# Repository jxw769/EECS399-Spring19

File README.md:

# EECS399_Spring19
Senior Project II for EECS399 in Spring 2019.

## Updated DDS Project 
In folder `DE10_Standard_AD9913`. Changed board to DE10 Standard from DE1. <br/>**See [DE10 setup](/DE10_Standard_AD9913/documentation/de10_setup.md) for the setup tutorial.**

EAGLE PCB Files and component datasheets are in `AD9913_PCB`.

## Bluetooth SPP Android App
`btspp.aia` is the Thunkable based Android app that can display scanning images via Bluetooth. Image data via Bluetooth is parsed to JSON from text format and converted to orignal PNG type from base64 JSON string. The app supports continous transmission and display of the scanning images, with a FPS around 0.5~1 due to Bluetooth transmission rate limit. *Can only be imported to [Thunkable Classic Platform](http://app.thunkable.com/?locale=en) (Not Cross Platform ver.).*

### How to use it
#### DE10 SoC Setup
* **Make sure DE10 switch setup is the same as below**
    </br>
* Boot up the Linux system.
* Configure Linux such that the device is paired and bluetooth SPP port is enabled. (See below and Ref)
* Execute
```cd ~/eecs399/bluetooth_send/ ```</br>
```./service.py```
  
#### Configuring Bluetooth on Linux
* Management of paired devices is done by bluetoothctl. (Configure etc/bluetooth/main.conf first)
* Once device is paired, we need to open up SPP upon reboot. A sample supervisor file can be found under `supervisor_conf`. If SPP port is not added, bluetooth transmission will not initiate. 
* Dependencies of service.py include PyBluez (for Python3).

#### Service.py
This file is written in mind that in the future, auto-detection of carotid function will be added to the service. The directory in which scanned image file is read and transmitted can be changed. 
One problem with this service file is that no time-out function is added. Therefore if a device is connected and not used (or, more likely, the app suddenly crashed without disconnecting the service), the service file will sit there forever, and must be restarted on Linux. This is not ideal for a product, and the best way is to add a time-out function, i.e. to have De10 automatically disconnect with the Android device if it doesn't receive any command from Android for a certain period of time. 

### Android App
* Press **Connect** to connect with a paired device (DE10 for current use).
* **Scan** to accept image data transmission via Bluetooth. Image are displayed in the (currently disabled) *Log* section. 
    * Scroll down *Log* to see activity history.
* **Stop** to stop accepting images. 
* **Proceed** to stop accepting images and proceed to the next task. 
* **Clear** to clear *Log* section and delete stored image data.
* **Disconnect** to disconnect from current connected device.

### Screenshots

### References
1. Thunkable Sample Bluetooth Chat App
`btchat.aia` is a sample Android app for Bluetooth SPP communication. It supports tranferring and receiving text data from connected devices. 
2. Used extensions: 
    * JSONTools: https://community.thunkable.com/t/free-jsontools-extension-version-4-released/5447
    * SimpleBase64: https://groups.google.com/d/msg/mitappinventortest/TAkRiwgY1yI/wQBnn6E0CwAJ
    * PyBluez
3. Configure Bluetooth on Linux
Here are some links that we found useful in setting up bluetooth:
    * Linux Bluetoothctl https://www.intel.com/content/dam/support/us/en/documents/edison/sb/edisonbluetooth_331704007.pdf
    * Setup SPP port (and use RFCOMM) https://unix.stackexchange.com/questions/92255/how-do-i-connect-and-send-data-to-a-bluetooth-serial-port-on-linux
    * Using PyBluez https://people.csail.mit.edu/albert/bluez-intro/x232.html

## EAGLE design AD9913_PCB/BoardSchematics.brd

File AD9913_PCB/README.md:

These are the most up-to-date EAGLE PCB files. 
One Problem with our design is that the comparator outputs needs to be pulled down to Vdd-2V, and we tried to use a linear regulator for this purpose. The problem is, however, that linear regulators cannot sink current, and therefore our comparator output would drag the 1.2 V linear regulator output to 3.3 V on which the comparator is run. One workaround is to add a small resistor from the linear regulator's output to ground, and therefore making the linear regulator always source current. This is not a good idea and is only a temporary workaround. Please redesign this part of the circuit.

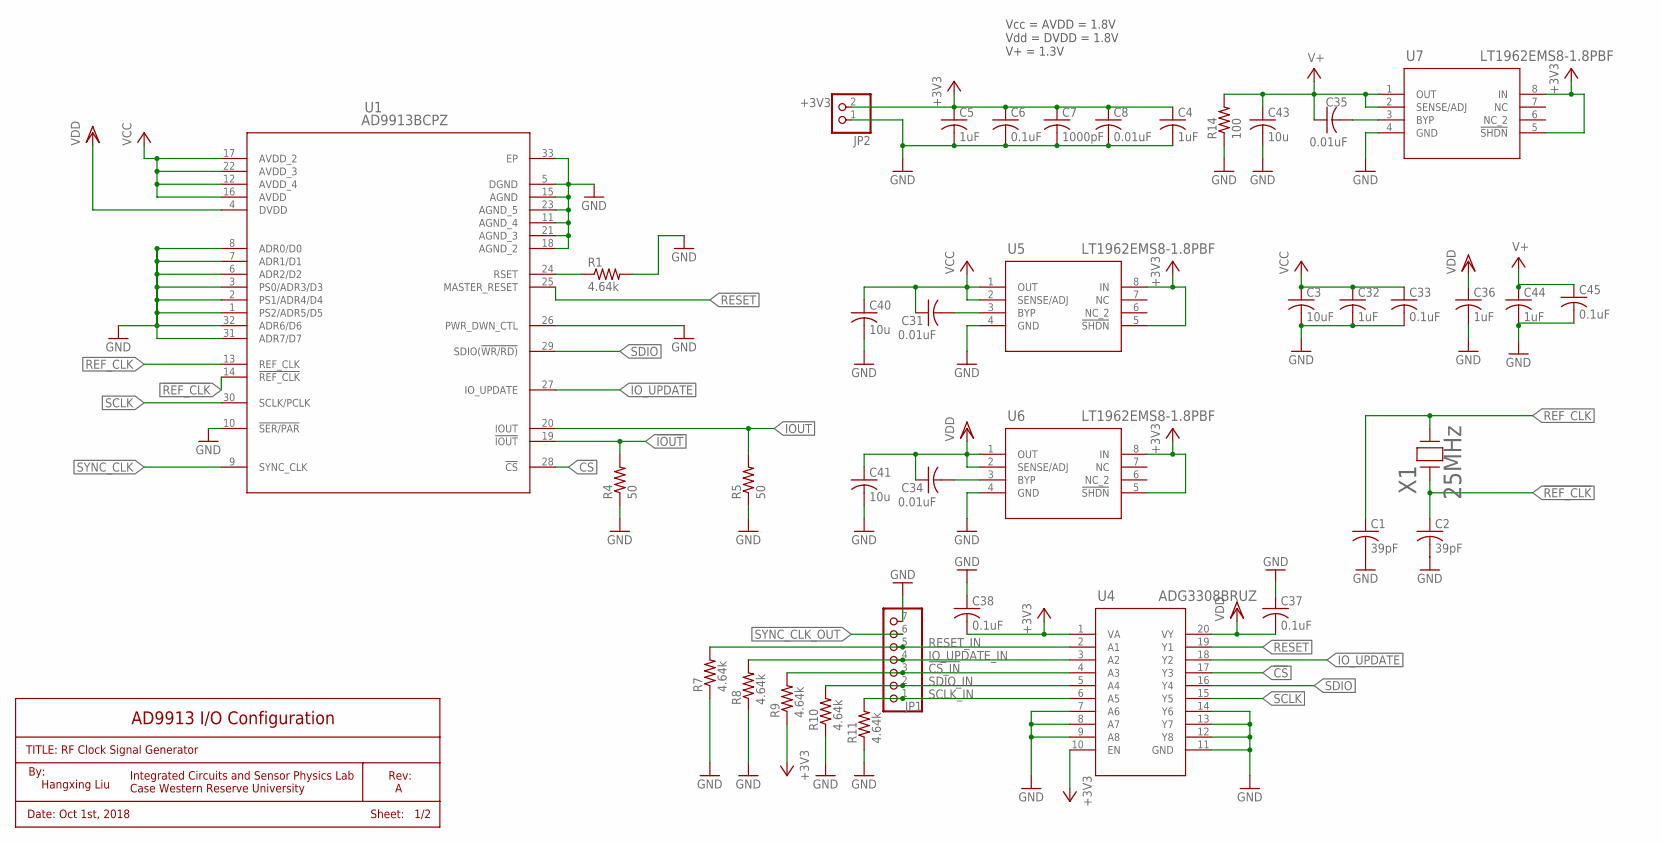
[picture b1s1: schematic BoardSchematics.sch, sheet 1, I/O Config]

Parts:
C1, C2: 39pF; C1608
C3: 10uF; C0603K
C4, C5, C32, C36, C44: 1uF; C0603K
C6, C33, C37, C38, C45: 0.1uF; C0603K
C7: 1000pF; C0603K
C8, C31, C34, C35: 0.01uF; C0603K
C40, C41, C43: 10u; C0603K
JP1: PINHD-1X7; 1X07
JP2: PINHD-1X2; 1X02
R1, R7, R8, R9, R10, R11: 4.64k; R0603
R4, R5: 50; R0603
R14: 100; R0603
U1: AD9913BCPZ; CP_32_2
U4: ADG3308BRUZ; RU_20
U5, U6, U7: LT1962EMS8-1.8PBF; MSOP-8_MS
X1: 25MHz; CRYSTAL_HC49SDLF

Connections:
!CS: U1.28 (!CS), U4.17 (Y3)
!CS_IN: JP1.3, R9.2, U4.4 (A3)
!IOUT: R4.2, U1.19 (!IOUT); also elsewhere on the board
!REF_CLK: C2.1, U1.14 (!REF_CLK), X1.1
+3V3: C4.1, C5.1, C6.1, C7.1, C8.1, C38.2, JP2.2, R9.1, U4.1 (VA), U4.10 (EN), U5.5 (!SHDN), U5.8 (IN), U6.5 (!SHDN), U6.8 (IN), U7.5 (!SHDN), U7.8 (IN); also elsewhere on the board
GND: C1.2, C2.2, C3.2, C4.2, C5.2, C6.2, C7.2, C8.2, C32.2, C33.2, C36.2, C37.1, C38.1, C40.2, C41.2, C43.2, C44.2, C45.2, JP1.7, JP2.1, R1.2, R4.1, R5.1, R7.1, R8.1, R10.1, R11.1, R14.1, U1.1 (PS2/ADR5/D5), U1.2 (PS1/ADR4/D4), U1.3 (PS0/ADR3/D3), U1.5 (DGND), U1.6 (ADR2/D2), U1.7 (ADR1/D1), U1.8 (ADR0/D0), U1.10 (!SER/PAR), U1.11 (AGND_4), U1.15 (AGND), U1.18 (AGND_2), U1.21 (AGND_3), U1.23 (AGND_5), U1.26 (PWR_DWN_CTL), U1.31 (ADR7/D7), U1.32 (ADR6/D6), U1.33 (EP), U4.7 (A6), U4.8 (A7), U4.9 (A8), U4.11 (GND), U4.12 (Y8), U4.13 (Y7), U4.14 (Y6), U5.4 (GND), U6.4 (GND), U7.4 (GND); also elsewhere on the board
IOUT: R5.2, U1.20 (IOUT); also elsewhere on the board
IO_UPDATE: U1.27 (IO_UPDATE), U4.18 (Y2)
IO_UPDATE_IN: JP1.4, R8.2, U4.3 (A2)
unnamed: R1.1, U1.24 (RSET)
unnamed: C31.2, U5.3 (BYP)
unnamed: C34.2, U6.3 (BYP)
unnamed: C35.2, U7.3 (BYP)
REF_CLK: C1.1, U1.13 (REF_CLK), X1.2
RESET: U1.25 (MASTER_RESET), U4.19 (Y1)
RESET_IN: JP1.5, R7.2, U4.2 (A1)
SCLK: U1.30 (SCLK/PCLK), U4.15 (Y5)
SCLK_IN: JP1.1, R11.2, U4.6 (A5)
SDIO: U1.29 (SDIO(!WR/RD)), U4.16 (Y4)
SDIO_IN: JP1.2, R10.2, U4.5 (A4)
SYNC_CLK: U1.9 (SYNC_CLK); also elsewhere on the board
SYNC_CLK_OUT: JP1.6; also elsewhere on the board
V+: C35.1, C43.1, C44.1, C45.1, R14.2, U7.1 (OUT), U7.2 (SENSE/ADJ); also elsewhere on the board
VCC: C3.1, C31.1, C32.1, C33.1, C40.1, U1.12 (AVDD_4), U1.16 (AVDD), U1.17 (AVDD_2), U1.22 (AVDD_3), U5.1 (OUT), U5.2 (SENSE/ADJ)
VDD: C34.1, C36.1, C37.2, C41.1, U1.4 (DVDD), U4.20 (VY), U6.1 (OUT), U6.2 (SENSE/ADJ)

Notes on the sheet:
AD9913 I/O Configuration
TITLE: RF Clock Signal Generator
By:
Hangxing Liu
Integrated Circuits and Sensor Physics Lab Case Western Reserve University
Rev: A
Date: Oct 1st, 2018
Sheet: 1/2
Vcc = AVDD = 1.8V Vdd = DVDD = 1.8V V+ = 1.3V

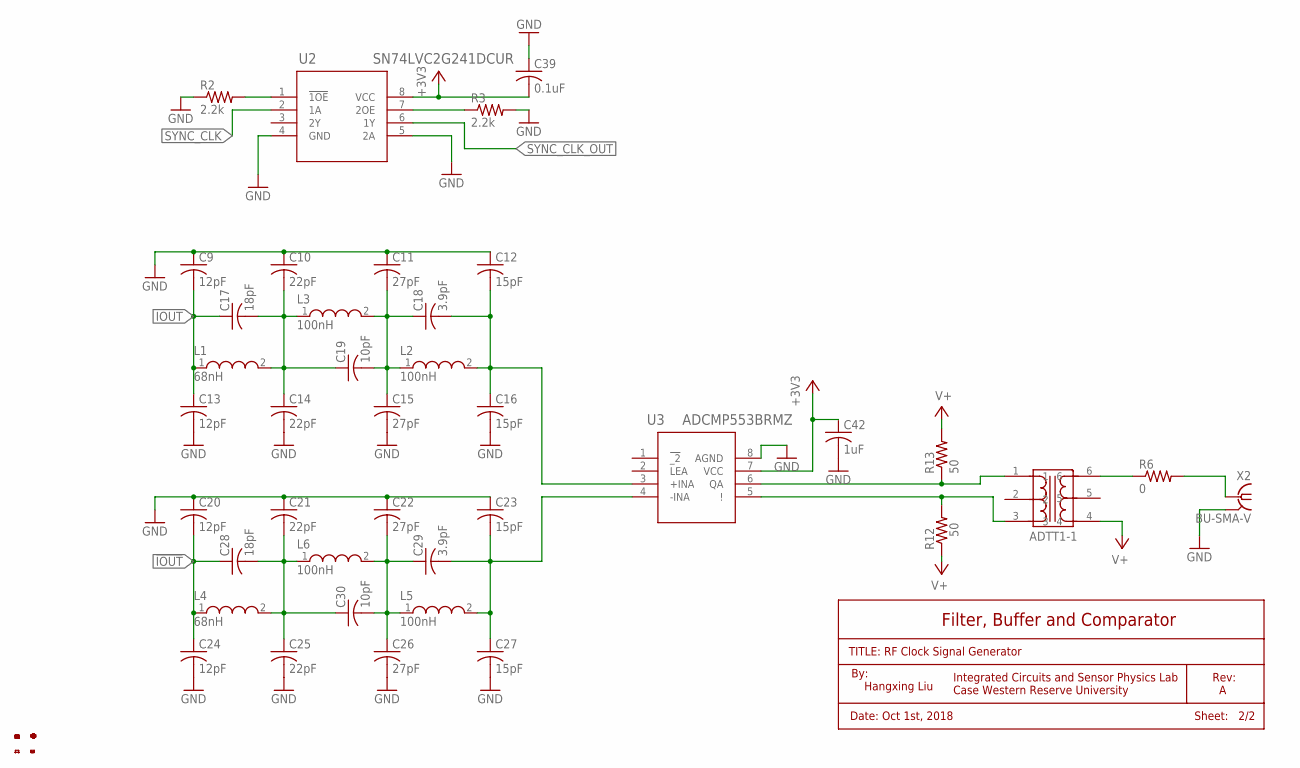
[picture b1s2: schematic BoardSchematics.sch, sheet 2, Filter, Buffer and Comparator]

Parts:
ATT1-1: PWB-1-CLCD542; CD542
C9, C13, C20, C24: 12pF; C0603K
C10, C14, C21, C25: 22pF; C0603K
C11, C15, C22, C26: 27pF; C0603K
C12, C16, C23, C27: 15pF; C0603K
C17, C28: 18pF; C0603K
C18, C29: 3.9pF; C0603K
C19, C30: 10pF; C0603K
C39: 0.1uF; C0603K
C42: 1uF; C0603K
L1, L4: 68nH; WE-PMI_1008
L2, L3, L5, L6: 100nH; WE-PMI_1008
R2, R3: 2.2k; R0603
R6: 0; R0603
R12, R13: 50; R0603
U2: SN74LVC2G241DCUR; DCU8
U3: ADCMP553BRMZ; RM_8
X2: BU-SMA-V

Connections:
!IOUT: C20.2, C24.1, C28.1, L4.1; also elsewhere on the board
+3V3: C39.2, C42.1, U2.8 (VCC), U3.7 (VCC); also elsewhere on the board
GND: C9.1, C10.1, C11.1, C12.1, C13.2, C14.2, C15.2, C16.2, C20.1, C21.1, C22.1, C23.1, C24.2, C25.2, C26.2, C27.2, C39.1, C42.2, R2.1, R3.2, U2.4 (GND), U2.5 (2A), U3.8 (AGND), X2.2, X2.3 (2), X2.4 (2), X2.5 (2); also elsewhere on the board
IOUT: C9.2, C13.1, C17.1, L1.1; also elsewhere on the board
unnamed: ATT1-1.1, R13.1, U3.6 (QA)
unnamed: ATT1-1.3, R12.2, U3.5 (!)
unnamed: ATT1-1.6, R6.1
unnamed: R6.2, X2.1
unnamed: R2.2, U2.1 (!1OE)
unnamed: C21.2, C25.1, C28.2, C30.1, L4.2, L6.1
unnamed: C10.2, C14.1, C17.2, C19.1, L1.2, L3.1
unnamed: R3.1, U2.7 (2OE)
unnamed: C11.2, C15.1, C18.1, C19.2, L2.1, L3.2
unnamed: C12.2, C16.1, C18.2, L2.2, U3.3 (+INA)
unnamed: C22.2, C26.1, C29.1, C30.2, L5.1, L6.2
unnamed: C23.2, C27.1, C29.2, L5.2, U3.4 (-INA)
SYNC_CLK: U2.2 (1A); also elsewhere on the board
SYNC_CLK_OUT: U2.6 (1Y); also elsewhere on the board
V+: ATT1-1.4, R12.1, R13.2; also elsewhere on the board

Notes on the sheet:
Filter, Buffer and Comparator
TITLE: RF Clock Signal Generator
By:
Hangxing Liu
Integrated Circuits and Sensor Physics Lab Case Western Reserve University
Rev: A
Date: Oct 1st, 2018
Sheet: 2/2
ADTT1-1

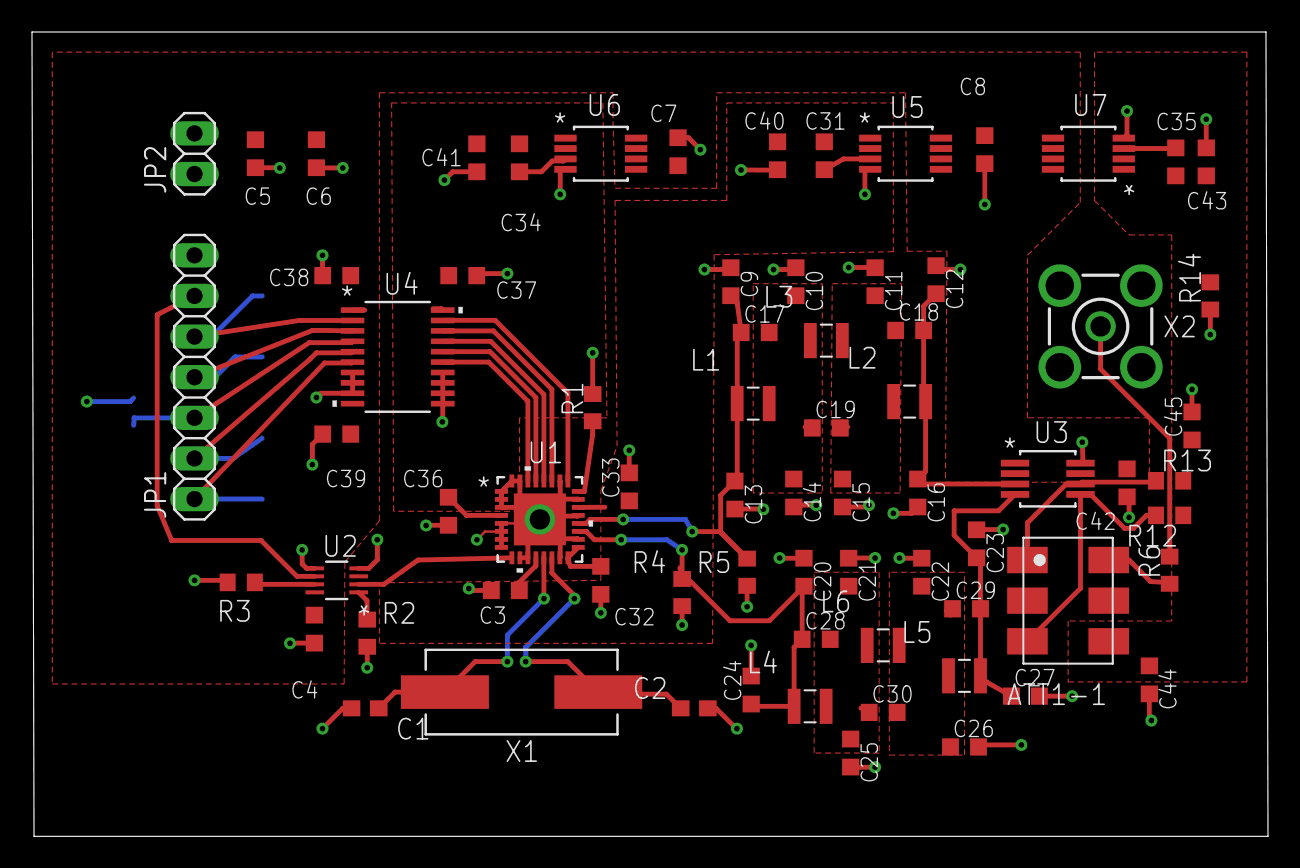
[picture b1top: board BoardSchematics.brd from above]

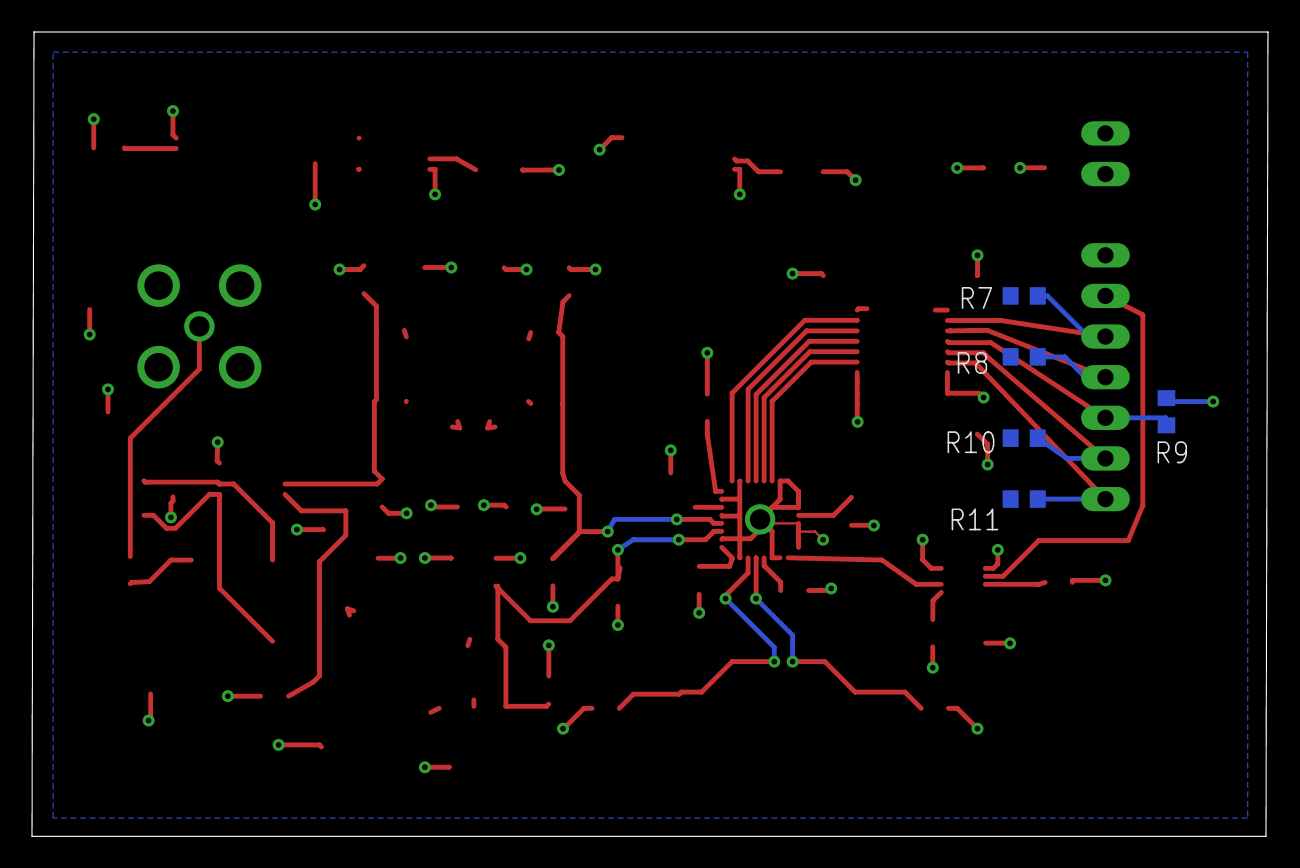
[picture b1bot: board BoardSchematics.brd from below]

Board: 2 copper layers, 77.3 x 50.3 mm, 77 parts (5 on the bottom side), 37 nets.

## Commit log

2019-02-06 Added sample project
2019-02-06 Added updated DDS project
2019-02-07 updated de10 compatibility
2019-02-21 Update setup documentation
2019-02-21 update documentation
2019-02-21 Thunkable sample app added
2019-02-21 update GUITest
2019-02-21 Include orginal DE1 project
2019-02-28 added test file
2019-02-28 setting repository ready for image reading.
2019-02-28 creating directory...
2019-03-01 Having a hard time serialize png file
2019-03-01 making development branch
2019-03-02 able to encode and decode png with base64
2019-03-19 finalizing test service prototype
2019-03-19 finalizing de10 bluetooth server
2019-03-19 finalizing bluetooth service
2019-03-19 remove uncessary files
2019-03-19 some tests...
2019-03-20 minor changes
2019-03-20 some tests
2019-03-27 update btspp with image display
2019-03-27 update de10 docs
2019-03-27 modification to service; new method and receive json
2019-03-27 cleanup
2019-04-01 using json for recieved msg
2019-04-04 updated with json
2019-04-04 update service
2019-04-13 finalizing project
2019-04-19 switch setup image added
2019-04-19 AD9913 PCB Files

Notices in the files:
parts and their libraries:
Wurth_Elektronik_Passive_rev15c: Copyright: Würth Elektronik
